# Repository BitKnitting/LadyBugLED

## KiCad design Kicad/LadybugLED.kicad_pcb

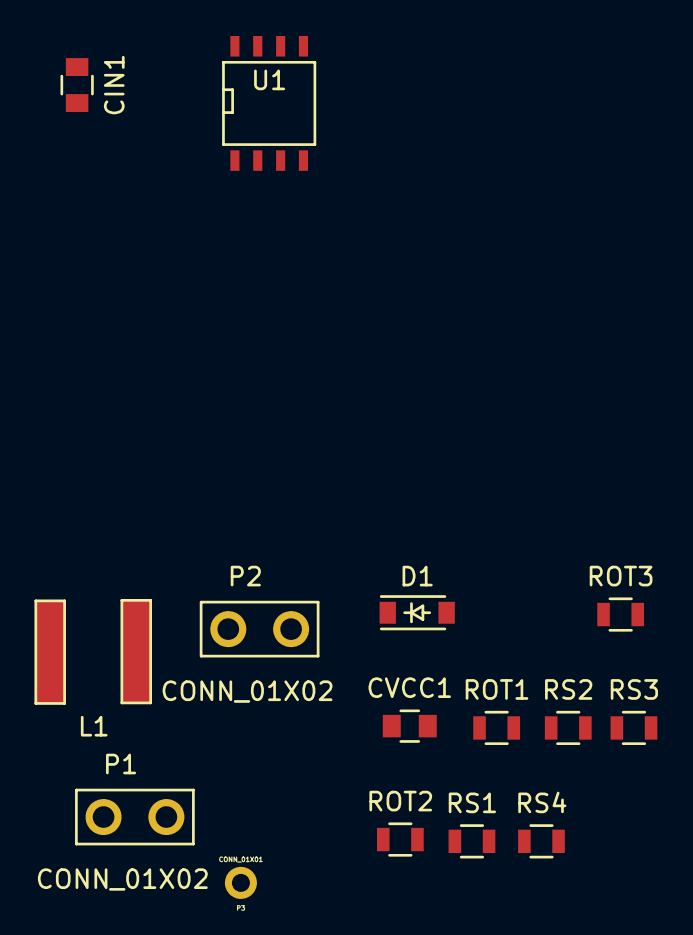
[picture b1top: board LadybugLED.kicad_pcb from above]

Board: 2 copper layers, 15 parts (0 on the bottom side), 10 nets, no tracks yet.

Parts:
CIN1: 4.7µF; C_0805
CVCC1: 1µ; C_0805
D1: D_Schottky; SOD-123
L1: 47µ; L-NR6045T470M
P1, P2: CONN_01X02; LB_CONN_2
P3: CONN_01X01; LB_CONN_1
ROT1, ROT2: 22K; R_0805
ROT3: 10K; R_0805
RS1, RS2, RS3: 1Ω; R_0805
RS4: 2.2Ω; R_0805
U1: NCL30160; SOIC-8-N

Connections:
GND: CIN1.2, CVCC1.2, P1.1, RS1.1, RS2.1, RS3.1, RS4.1, U1.3
unnamed: CIN1.1, D1.1, P1.2, P2.1, U1.7
unnamed: CVCC1.1, ROT3.2, U1.4
unnamed: D1.2, L1.1, U1.8
unnamed: L1.2, P2.2
unnamed: P3.1, U1.6
unnamed: ROT1.1, U1.5
unnamed: ROT1.2, ROT2.1
unnamed: ROT2.2, ROT3.1
unnamed: RS1.2, RS2.2, RS3.2, RS4.2, U1.1, U1.2

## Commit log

2015-04-05 added renameGerbers Automator workflow and layout
2016-01-26 buck regulator LED driver - first commit
